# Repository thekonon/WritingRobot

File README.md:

# WritingRobot
Draw anything using robot!

## Overview

Robot is made of:
- Control part that runs on __Raspberry PI4__
- CAN communication using __MPC2515__ modules
- <del>__Arduino__ Nano clone</del>
- STM32 Bluepill (STM32F103C6T6
- Two __stepper motors drivers__

# Schemes

## Electrical wiring

Arduino:

Stepper motors

Powerline

MCP2551 CANH/L -> Rx/Tx data module

L7805 -> 12V -> 5V/1A 

## Board design

Wiring scheme of actual PCB

3D view to the board without and with modules

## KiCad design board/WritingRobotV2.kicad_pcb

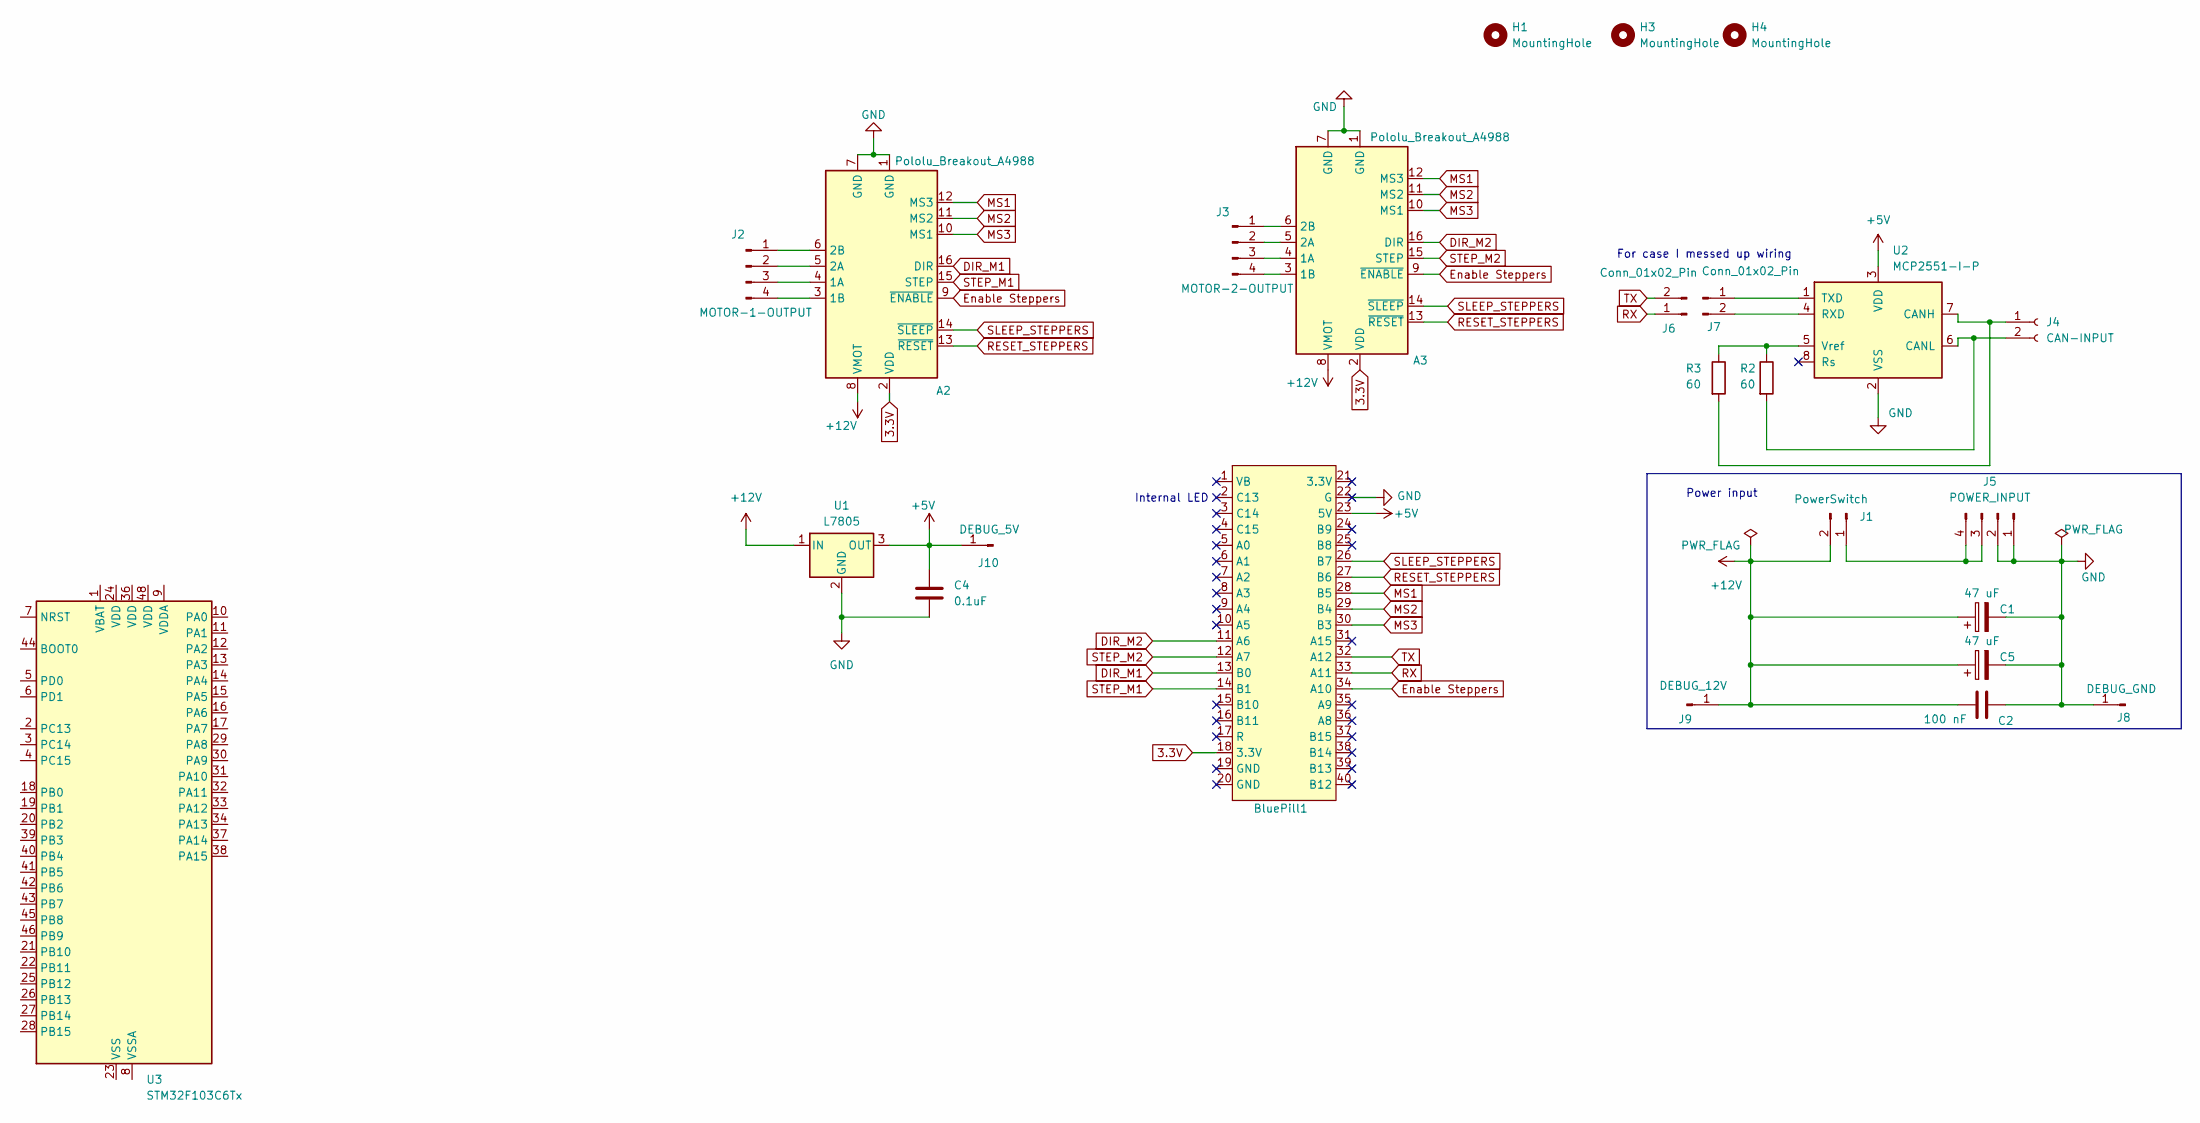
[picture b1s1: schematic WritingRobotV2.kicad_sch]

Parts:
A2, A3: Pololu_Breakout_A4988; Pololu_Breakout-16_15.2x20.3mm
BluePill1: BluePill
C1, C5: 47 uF; C_Radial_D8.0mm_H11.5mm_P3.50mm
C2: 100 nF; C_Disc_D3.0mm_W2.0mm_P2.50mm
C4: 0.1uF; C_Disc_D3.8mm_W2.6mm_P2.50mm
H1, H3, H4: MountingHole; MountingHole_4.3mm_M4
J1: PowerSwitch; PinHeader_1x02_P2.54mm_Vertical
J2: MOTOR-1-OUTPUT; PinHeader_1x04_P2.54mm_Vertical
J3: MOTOR-2-OUTPUT; PinHeader_1x04_P2.54mm_Vertical
J4: CAN-INPUT; PinSocket_1x02_P2.54mm_Vertical
J5: POWER_INPUT; PinHeader_1x04_P2.54mm_Vertical
J6, J7: Conn_01x02_Pin; PinHeader_1x02_P2.54mm_Vertical
J8: DEBUG_GND; PinHeader_1x01_P2.54mm_Vertical
J9: DEBUG_12V; PinHeader_1x01_P2.54mm_Vertical
J10: DEBUG_5V; PinHeader_1x01_P2.54mm_Vertical
R2, R3: 60; R_Axial_DIN0204_L3.6mm_D1.6mm_P7.62mm_Horizontal
U1: L7805; TO-220-3_Vertical
U2: MCP2551-I-P; DIP-8_W7.62mm
U3: STM32F103C6Tx; LQFP-48_7x7mm_P0.5mm

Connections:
3.3V: A2.2 (VDD), A3.2 (VDD), BluePill1.18 (3.3V)
+5V: BluePill1.23 (5V), C4.1, J10.1, U1.3 (OUT), U2.3 (VDD)
+12V: A2.8 (VMOT), A3.8 (VMOT), C1.1, C2.1, C5.1, J1.2, J9.1, U1.1 (IN)
DIR_M1: A2.16 (DIR), BluePill1.13 (B0)
DIR_M2: A3.16 (DIR), BluePill1.11 (A6)
Enable Steppers: A2.9 (~ENABLE), A3.9 (~ENABLE), BluePill1.34 (A10)
GND: A2.1 (GND), A2.7 (GND), A3.1 (GND), A3.7 (GND), BluePill1.22 (G), C1.2, C2.2, C4.2, C5.2, J5.1, J5.2, J8.1, U1.2 (GND), U2.2 (VSS)
MS1: A2.12 (MS3), A3.12 (MS3), BluePill1.28 (B5)
MS2: A2.11 (MS2), A3.11 (MS2), BluePill1.29 (B4)
MS3: A2.10 (MS1), A3.10 (MS1), BluePill1.30 (B3)
unnamed: A2.4 (1A), J2.3
unnamed: A2.3 (1B), J2.4
unnamed: A2.5 (2A), J2.2
unnamed: A2.6 (2B), J2.1
unnamed: A3.4 (1A), J3.3
unnamed: A3.3 (1B), J3.4
unnamed: A3.5 (2A), J3.2
unnamed: A3.6 (2B), J3.1
unnamed: J1.1, J5.3, J5.4
unnamed: J4.1, R3.2, U2.7 (CANH)
unnamed: J4.2, R2.2, U2.6 (CANL)
unnamed: J7.1, U2.1 (TXD)
unnamed: J7.2, U2.4 (RXD)
unnamed: R2.1, R3.1, U2.5 (Vref)
unnamed: U3.23 (VSS), U3.35 (VSS), U3.47 (VSS)
RESET_STEPPERS: A2.13 (~RESET), A3.13 (~RESET), BluePill1.27 (B6)
RX: BluePill1.33 (A11), J6.1
SLEEP_STEPPERS: A2.14 (~SLEEP), A3.14 (~SLEEP), BluePill1.26 (B7)
STEP_M1: A2.15 (STEP), BluePill1.14 (B1)
STEP_M2: A3.15 (STEP), BluePill1.12 (A7)
TX: BluePill1.32 (A12), J6.2

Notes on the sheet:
Internal LED
Power input
For case I messed up wiring

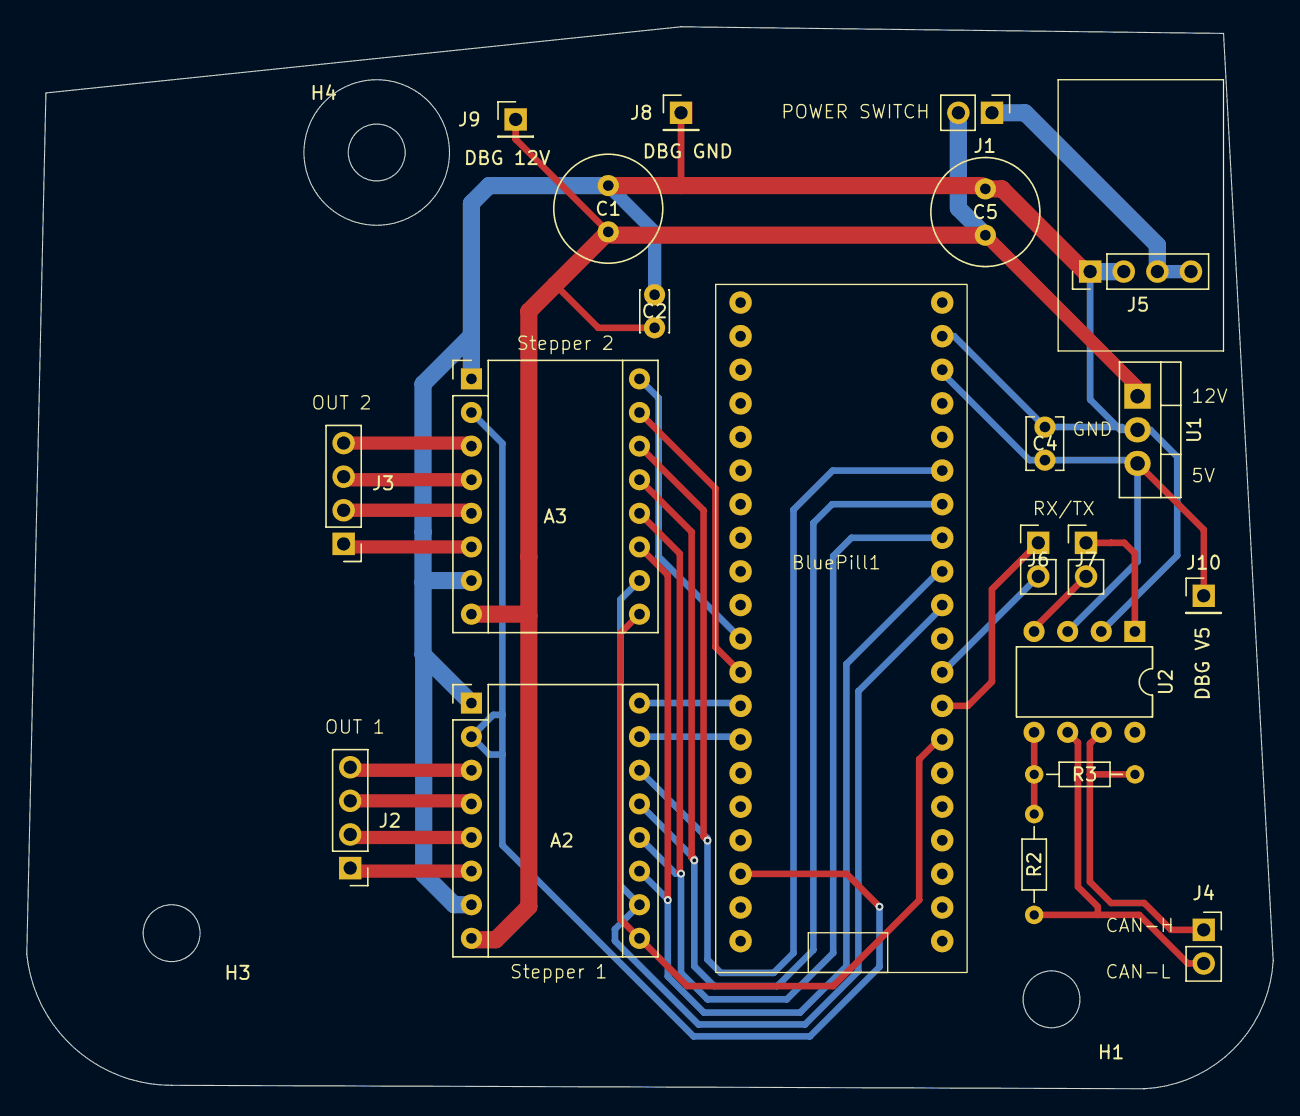
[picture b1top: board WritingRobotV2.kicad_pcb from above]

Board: 2 copper layers, 94.2 x 80.3 mm, 24 parts (0 on the bottom side), 30 nets.

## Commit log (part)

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2024-04-14 hotfix
2024-04-16 - Added second dial - Calculation moved to _calculations.py
2024-04-21 Calculations moved to _calculations.py
2024-04-21 README.md modified Added requirements.txt
2024-04-21 Removed black photo + Examples
2024-04-21 Create python-package.yml
    First time testing this feature
2024-04-21 Black formatter aplied
2024-04-21 added tests for automatic testing
2024-04-21 Tried to add comments using copilot
2024-04-21 Updated gitignore, refactored tools using AI
2024-04-21 Docstring added to tools
2024-04-25 Init commit for files of first board iteration
2024-04-26 Updated requirements.txt - added python can
2024-04-26 Added files for docu - readme
2024-04-26 Removed pywin32 from requirements
2024-04-26 Pytest added to requirements.txt
2024-04-26 Tests moved to test folder
2024-04-26 Files moved to control
2024-04-26 Restructured Main moved
2024-04-26 Removed unused testes Added new test file for calculations
2024-04-26 Removed backups from git
2024-04-26 GitIgnore edited
2024-04-26 Update python-package.yml
    Added library for PySide
2024-04-26 Update python-package.yml
    Another attempt for testing PySide
2024-04-26 Update python-package.yml
    Another attempt
2024-04-26 Update python-package.yml
    next
2024-04-30 Added robot class, refactor
2024-04-30 Test for robot calculation
2024-04-30 Update python-package.yml
    Added test for python 3.6 and 3.12
2024-04-30 Updating requirements.txt due to the missing matplotlib
2024-04-30 Update python-package.yml
    removed python 3.6
2024-05-08 Changed electrical layout Added 3d components to PCB Created photos for DOCU Modified Readme file
2024-05-08 Project saved
2024-05-15 Added function value_to_hex_2 that imeplements idea from
    https://github.com/thekonon/WritingRobot/issues/7
2024-05-19 Refactor started
2024-05-19 Refactor continue
2024-05-19 Edited tests, adding autopath for settings file
2024-05-19 Using autogenerated file from degigner instead of my.py
2024-05-19 Working robot
2024-05-19 Minor changes
2024-05-25 Removed float annotation
2024-05-25 Annotation added to _tools
2024-05-25 Paint removed
2024-05-25 Annotation added to main
2024-05-25 main_gui reformated
2024-05-25 HotFix for tests
2024-05-25 Updated requirements.txt bat for venv added
2024-05-25 Drawer again restructured
2024-05-25 Graphics merged to one file
2024-05-25 Resolving errors from pylance
2024-05-25 Resolving another Qt problems
2024-05-25 Imgs moved to Docu folder
2024-05-25 diagram.json removed - old file, not used anymore
2024-05-25 Imports resolving
2024-05-29 Working on new design
2024-05-29 quick fix of sending msg
2024-05-29 Another quick fix
2024-05-29 Added msg sending on drag
2024-05-29 Diagnostig msg
2024-05-29 Helpers modified - wrong ranges
2024-06-01 Added type ignore
2024-06-01 Gui reworked, it looks better, CAN features connected
2024-06-01 Regenerated requirements.txt
2024-06-01 tests repaired, pywin32 removed - raspberry installation problems
2024-06-01 Updated CAN frame calculation
2024-06-11 Board updated
2024-06-15 Minor changes in board
2024-06-15 Added folder for arduino function, CMakeLists.txt contains includes for test
2024-06-15 Remove junk in test/test_helpers.py Added electronics_calculations/main.py for calculation of analog filter
2024-06-15 Added build folder to ignore
2024-06-15 Test module added - delete it afterwards
2024-06-15 Added unity as submodule
2024-06-15 Removed test submodule
2024-06-15 MCP2515 submodule added
2024-06-15 Arduino constants moved to constants Created constants.h file
2024-06-15 functions for arduino control moving to src folder unit tests added
2024-06-15 Adding new module for controlling the motor
2024-06-18 Rename c->cpp
2024-06-18 non - working - saving the progress
2024-06-18 Compilation in arduino IDE is working
2024-06-20 Minor changes in arduino code
2024-06-20 Updated the source files
2024-06-20 PlatformIO project added
2024-06-20 requirements.txt updated
2024-06-21 Added tests
2024-06-21 Test for arduino are working in Platformio
2024-06-21 Removed arduino folder
2024-06-21 changed fixed version of MCP2515 to submodule
2024-06-21 Pywin removed from requirements.txt
2024-06-21 Python 3.9 -> python 3.10
    Python 3.9 was not able to take my type hints
2024-07-13 [No functional changes] Docu renamed to docu
2024-07-13 Constants moved to separated file
2024-07-13 [No functional change] removed sys agument from main
2024-07-13 [No functional change] Added Makefile and lib folder to gitignore
2024-07-13 Constants moved from settings.yaml to constants.py
2024-07-13 Saving progress before creating new branch
2024-07-13 Work on testing robot
2024-07-14 added logging deleted drawer robot computation rework added testing awkward scenarios
2024-07-14 [TESTS OK] Mixins introduced
2024-08-11 Mixin usage applied, tests added
2024-08-11 Board to stm32
2024-08-16 Saving current work
2024-08-17 Reworking it again in src folder
2024-08-17 Added second pic for wiki
2024-08-24 Working gui with basic limits
2024-09-25 Docu update after going to STM32 chip
2024-09-25 Board updated to STM32
    Other files in rework
2024-09-25 Update README.md
    Docu -> dociu
2024-09-25 Update README.md
    Update front page arduino -> STM32
2024-09-25 Update README.md
    Removed MPC2515
2024-09-27 This was send to manufactory
2024-10-14 Added img for traectory planning
2024-10-29 Added imgs to docu
2024-11-10 Adding everything
2024-11-11 Implemented tests for setting acceleration
2024-11-11 Tests for setting up the diff phi done
2025-02-22 Methods renamed
2025-02-22 TCurve->SCurve file rename
2025-02-22 Comments fixed
2025-02-22 Test was renamed
2025-02-22 Work on SCurve in TCurve continiue
2025-03-02 Added imgs for TCurve
2025-04-06 Saving work before using TCurve submodule
2025-10-26 Project restructu
2025-10-26 remove trash, relocate create_virt_env.bat
2025-10-27 add stm32 project
2025-10-28 Fix img links
2025-11-18 clean main.py
2025-11-18 move setup logger to logging
2025-11-18 comment out test
2025-11-18 linting, removing unused imports
2025-11-18 Fix linter errors/warnings
2025-11-18 rerun linter
2025-11-18 logger fixed
2025-11-18 class changed to factory, knob added
2025-11-18 circle intersetion output anotation change to not optional, if it fails, it raises value error
